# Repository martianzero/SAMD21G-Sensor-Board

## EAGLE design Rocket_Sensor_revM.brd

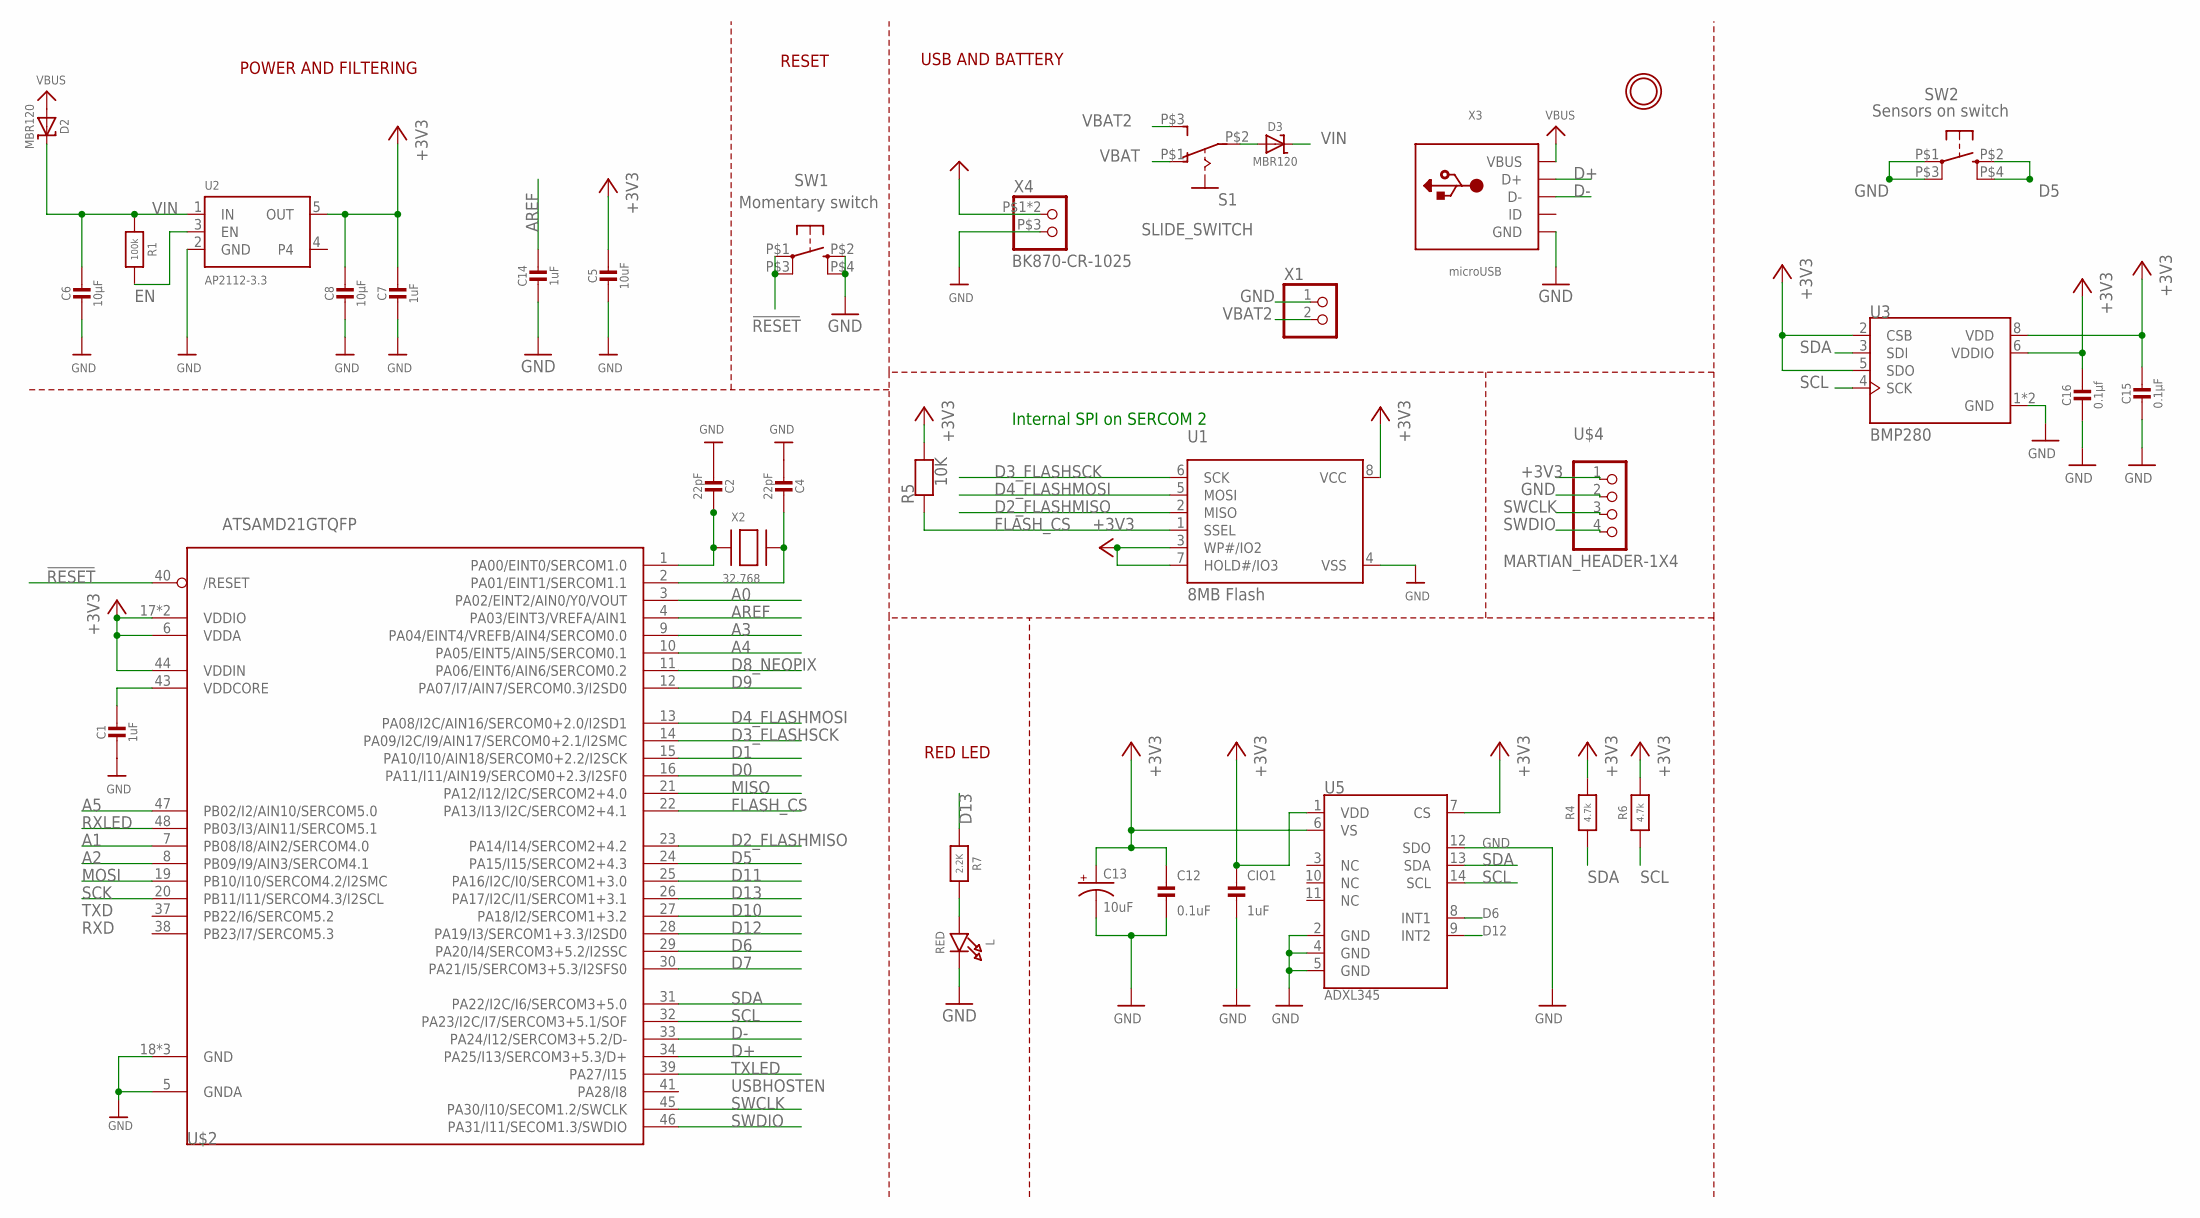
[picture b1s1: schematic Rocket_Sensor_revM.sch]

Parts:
C1, C7, C14: 1uF; MICROBUILDER__1206
C2, C4: 22pF; MICROBUILDER__1206
C5: 10uF; MICROBUILDER__1206
C6, C8: 10µF; MICROBUILDER__1206
C12: 0.1uF; MICROBUILDER__1206
C13: 10uF; EIA3216
C15: 0.1µF; MICROBUILDER__1206
C16: 0.1µf; MICROBUILDER__1206
CIO1: 1uF; MICROBUILDER__1206
D2, D3: MBR120; MICROBUILDER_SOD-123
L: RED; MICROBUILDER_CHIPLED_1206
R1: 100k; MICROBUILDER__0805
R4, R6: 4.7k; MICROBUILDER__0805
R5: 10K; MICROBUILDER__0805
R7: 2.2K; MICROBUILDER__0805
S1: SLIDE_SWITCH; MSK12C02_SLIDE_SWITCH
SW1: Momentary switch; ALIEXPRESS_WHITE_TACTILE_PUSHBUTTON
SW2: Sensors on switch; ALIEXPRESS_WHITE_TACTILE_PUSHBUTTON
U1: 8MB Flash; MICROBUILDER_SOIC8_208MIL
U2: AP2112-3.3; MICROBUILDER_SOT23-5
U3: BMP280; XDCR_BMP280
U5: ADXL345; LGA-14
U$2: ATSAMD21GTQFP; TQFP-48
U$4: MARTIAN_HEADER-1X4; MARTIAN_1X4_ROUND
U$7: MICROBUILDER_MOUNTINGHOLE2.0; MICROBUILDER_MOUNTINGHOLE_2.0_PLATED
X1: MICROBUILDER_CON_JST_PH_2PIN; MICROBUILDER_JSTPH2
X2: 32.768; ADAFRUIT2_XTAL3215
X3: microUSB; ALIEXPRESS_MICROUSB_RECEPTICLE_V2
X4: BK870-CR-1025; BK870-CR-1025_COIN_CELL_RETAINER

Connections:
!RESET: SW1.P$1, SW1.P$3 (P1), U$2.40 (/RESET)
+3V3: C5.1, C7.1, C8.1, C12.1, C13.+, C15.1, C16.1, CIO1.1, R4.2, R5.2, R6.2, U1.3 (WP#/IO2), U1.7 (HOLD#/IO3), U1.8 (VCC), U2.5 (OUT), U3.2 (CSB), U3.5 (SDO), U3.6 (VDDIO), U3.8 (VDD), U5.1 (VDD), U5.6 (VS), U5.7 (CS), U$2.6 (VDDA), U$2.17 (VDDIO), U$2.36 (VDDIO), U$2.44 (VDDIN), U$4.1 (9)
A0: U$2.3 (PA02/EINT2/AIN0/Y0/VOUT)
A1: U$2.7 (PB08/I8/AIN2/SERCOM4.0)
A2: U$2.8 (PB09/I9/AIN3/SERCOM4.1)
A3: U$2.9 (PA04/EINT4/VREFB/AIN4/SERCOM0.0)
A4: U$2.10 (PA05/EINT5/AIN5/SERCOM0.1)
A5: U$2.47 (PB02/I2/AIN10/SERCOM5.0)
AREF: C14.1, U$2.4 (PA03/EINT3/VREFA/AIN1)
D0: U$2.16 (PA11/I11/AIN19/SERCOM0+2.3/I2SF0)
D1: U$2.15 (PA10/I10/AIN18/SERCOM0+2.2/I2SCK)
D2_FLASHMISO: U1.2 (MISO), U$2.23 (PA14/I14/SERCOM2+4.2)
D3_FLASHSCK: U1.6 (SCK), U$2.14 (PA09/I2C/I9/AIN17/SERCOM0+2.1/I2SMC)
D4_FLASHMOSI: U1.5 (MOSI), U$2.13 (PA08/I2C/AIN16/SERCOM0+2.0/I2SD1)
D5: SW2.P$2 (S), SW2.P$4 (S1), U$2.24 (PA15/I15/SERCOM2+4.3)
D6: U5.8 (INT1), U$2.29 (PA20/I4/SERCOM3+5.2/I2SSC)
D7: U$2.30 (PA21/I5/SERCOM3+5.3/I2SFS0)
D8_NEOPIX: U$2.11 (PA06/EINT6/AIN6/SERCOM0.2)
D9: U$2.12 (PA07/I7/AIN7/SERCOM0.3/I2SD0)
D10: U$2.27 (PA18/I2/SERCOM1+3.2)
D11: U$2.25 (PA16/I2C/I0/SERCOM1+3.0)
D12: U5.9 (INT2), U$2.28 (PA19/I3/SERCOM1+3.3/I2SD0)
D13: R7.1, U$2.26 (PA17/I2C/I1/SERCOM1+3.1)
D+: U$2.34 (PA25/I13/SERCOM3+5.3/D+), X3.D+
D-: U$2.33 (PA24/I12/SERCOM3+5.2/D-), X3.D-
EN: R1.2, U2.3 (EN)
FLASH_CS: R5.1, U1.1 (SSEL), U$2.22 (PA13/I13/I2C/SERCOM2+4.1)
GND: C1.2, C2.2, C4.2, C5.2, C6.2, C7.2, C8.2, C12.2, C13.-, C14.2, C15.2, C16.2, CIO1.2, L.C, SW1.P$2 (S), SW1.P$4 (S1), SW2.P$1, SW2.P$3 (P1), U1.4 (VSS), U2.2 (GND), U3.1 (GND), U3.7 (GND), U5.2 (GND), U5.4 (GND), U5.5 (GND), U5.12 (SDO), U$2.5 (GNDA), U$2.18 (GND), U$2.35 (GND), U$2.42 (GND), U$4.2 (10), X1.1, X3.GND, X3.P$6 (GND), X3.P$7 (GND), X3.P$8 (GND), X3.P$9 (GND), X4.P$3 (GND)
MISO: U$2.21 (PA12/I12/I2C/SERCOM2+4.0)
MOSI: U$2.19 (PB10/I10/SERCOM4.2/I2SMC)
unnamed: D3.A, S1.P$2
unnamed: L.A, R7.2
unnamed: C2.1, U$2.1 (PA00/EINT0/SERCOM1.0), X2.P$1
unnamed: C4.1, U$2.2 (PA01/EINT1/SERCOM1.1), X2.P$2
RXLED: U$2.48 (PB03/I3/AIN11/SERCOM5.1)
SCK: U$2.20 (PB11/I11/SERCOM4.3/I2SCL)
SCL: R6.1, U3.4 (SCK), U5.14 (SCL), U$2.32 (PA23/I2C/I7/SERCOM3+5.1/SOF)
SDA: R4.1, U3.3 (SDI), U5.13 (SDA), U$2.31 (PA22/I2C/I6/SERCOM3+5.0)
SWCLK: U$2.45 (PA30/I10/SECOM1.2/SWCLK), U$4.3 (11)
SWDIO: U$2.46 (PA31/I11/SECOM1.3/SWDIO), U$4.4 (12)
TXLED: U$2.39 (PA27/I15)
VBAT: S1.P$1 (O), X4.P$1 (VBAT), X4.P$2 (VBAT)
VBAT2: S1.P$3 (S), X1.2
VBUS: D2.A, X3.VBUS
VDDCORE: C1.1, U$2.43 (VDDCORE)
VIN: C6.1, D2.C, D3.C, R1.1, U2.1 (IN)

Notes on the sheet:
POWER AND FILTERING
RESET
USBHOSTEN
TXD
RXD
USB AND BATTERY
RED LED
Internal SPI on SERCOM 2

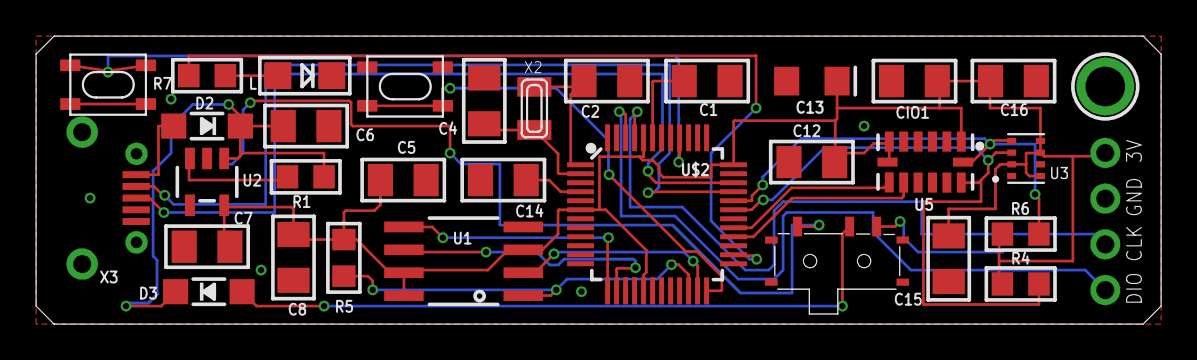
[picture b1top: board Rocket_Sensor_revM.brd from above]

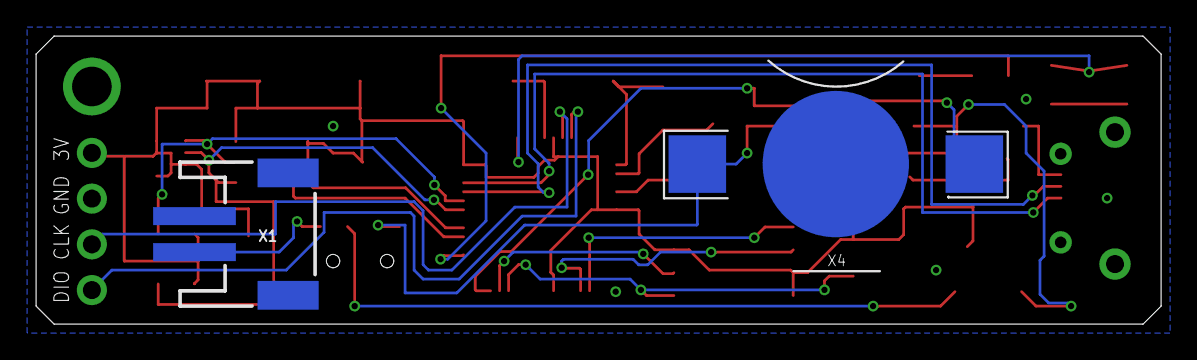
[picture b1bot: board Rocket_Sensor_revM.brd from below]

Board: 2 copper layers, 62.5 x 16.0 mm, 35 parts (2 on the bottom side), 28 nets.

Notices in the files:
parts and their libraries:
microbuilder: This work is placed in the public domain, and may be freely used for commercial and non-commercial work with the following conditions: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
SparkFun-Aesthetics: Licensing: Creative Commons ShareAlike 4.0 International - https://creativecommons.org/licenses/by-sa/4.0
